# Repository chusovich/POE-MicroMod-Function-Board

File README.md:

# POE-MicroMod-Function-Board
a minimal W5500-based POE ethernet board for the MicroMod ecosystem

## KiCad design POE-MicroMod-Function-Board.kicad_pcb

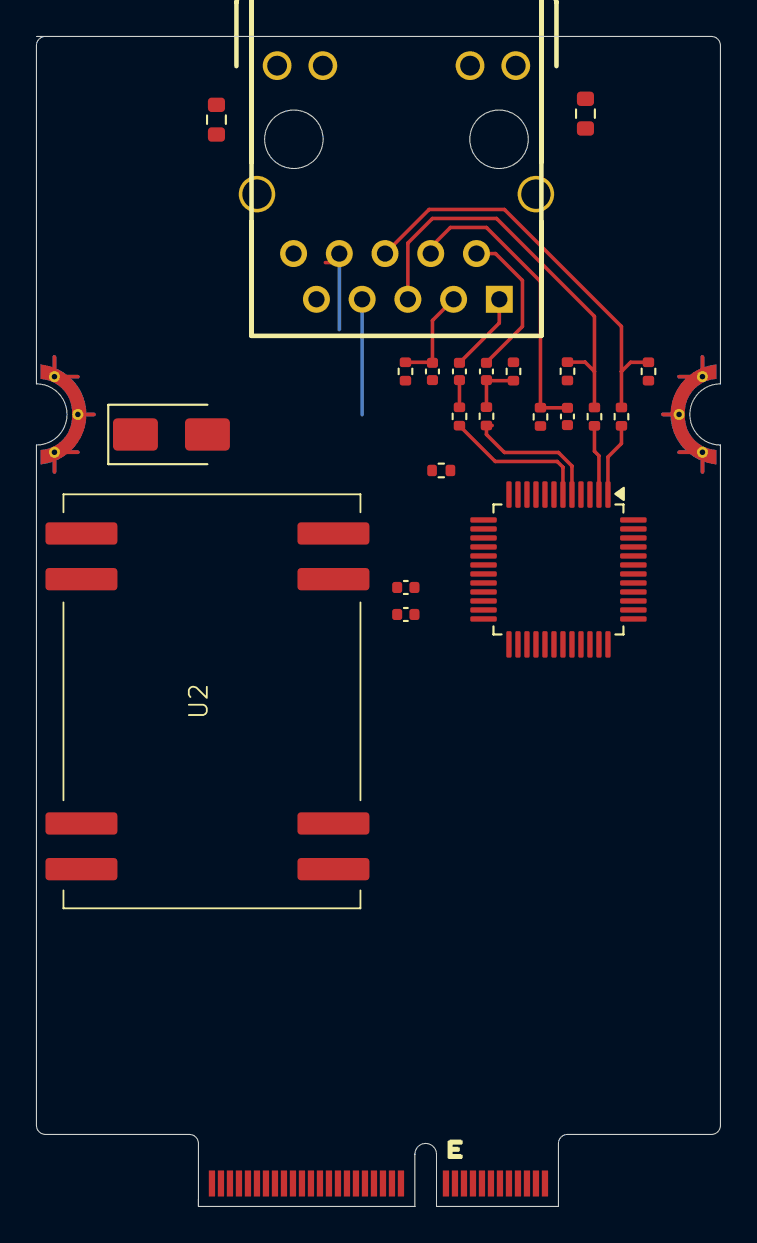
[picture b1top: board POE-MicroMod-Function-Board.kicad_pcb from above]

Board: 2 copper layers, 38.0 x 65.0 mm, 23 parts (0 on the bottom side), 31 nets.

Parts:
C1: 10nF; C_0402_1005Metric
C2: 4.7uF; C_0402_1005Metric
C5, C6: 6.8n; C_0402_1005Metric
C7: 10n; C_0402_1005Metric
C8: 22u; C_0402_1005Metric
D1: SMAJ58A; D_SMA
J1: M.2-CARD-E-22_FUNCTION_STANDARD
R1: 12.4k; R_0402_1005Metric
R2, R3, R6, R7: 33; R_0402_1005Metric
R4, R5, R8, R9, R10: 49.9; R_0402_1005Metric
R11, R12: 330; R_0603_1608Metric
RJ1: HY931147C; RJ45-TH_HY931147C
U1: W5500; LQFP-48_7x7mm_P0.5mm
U2: DM9900_5V

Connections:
/3.3V: J1.73 (3.3V), R8.2, R9.2, R10.2, RJ1.12, RJ1.14
/5V: U2.1 (VCC+), U2.2 (VCC+)
/ACTIVE_LED: R12.1, U1.27 (ACTLED)
/CS: J1.49 (F1/~CS), U1.32 (~SCS)
/INT: J1.47 (F0/~INT), U1.36 (~INT)
/LINK_LED: R11.2, U1.25 (LINKLED)
/MISO: J1.7 (SPI_SDO), U1.34 (MISO)
/MOSI: J1.5 (SPI_SDI), U1.35 (MOSI)
/POE+: D1.1 (A1), RJ1.7, U2.5 (VIN+), U2.6 (VIN+)
/POE-: D1.2 (A2), RJ1.8, U2.7 (VIN-)
/RST: J1.51 (F2/PWM), U1.37 (~RST)
/RX_N: R2.1, U1.5 (RXN)
/RX_P: R3.1, U1.6 (RXP)
/SCLK: J1.3 (SPI_SCK), U1.33 (SCLK)
/TX_N: R6.1, U1.1 (TXN)
/TX_P: R7.1, U1.2 (TXP)
GND: C1.2, C2.2, C7.2, C8.2, J1.1 (GND), J1.2 (GND), J1.8 (GND), J1.33 (GND), J1.39 (GND), J1.45 (GND), J1.75 (GND), R1.2, RJ1.9, RJ1.10, RJ1.GND1 (GND), RJ1.GND2 (GND), U1.3 (AGND), U1.9 (AGND), U1.14 (AGND), U1.16 (AGND), U1.19 (AGND), U1.29 (GND), U1.48 (AGND)
unnamed: C5.1, R2.2, R5.1
unnamed: C5.2, RJ1.2
unnamed: C6.1, R3.2, R4.1
unnamed: C6.2, RJ1.1
unnamed: C7.1, R4.2, R5.2, RJ1.3
unnamed: C8.1, R10.1, RJ1.4
unnamed: R6.2, R8.1, RJ1.6
unnamed: R7.2, R9.1, RJ1.5
unnamed: R11.1, RJ1.11
unnamed: R12.2, RJ1.13
unnamed: C1.1, U1.22 (1V2O)
unnamed: U1.4 (AVDD), U1.8 (AVDD), U1.11 (AVDD), U1.15 (AVDD), U1.17 (AVDD), U1.21 (AVDD)
unnamed: R1.1, U1.10 (EXRES1)
unnamed: C2.1, U1.20 (TOCAP)

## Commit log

2025-08-22 started schematic
2025-08-22 refreshed libraries
2025-08-22 updated libraries
2025-08-22 started routing pcb
